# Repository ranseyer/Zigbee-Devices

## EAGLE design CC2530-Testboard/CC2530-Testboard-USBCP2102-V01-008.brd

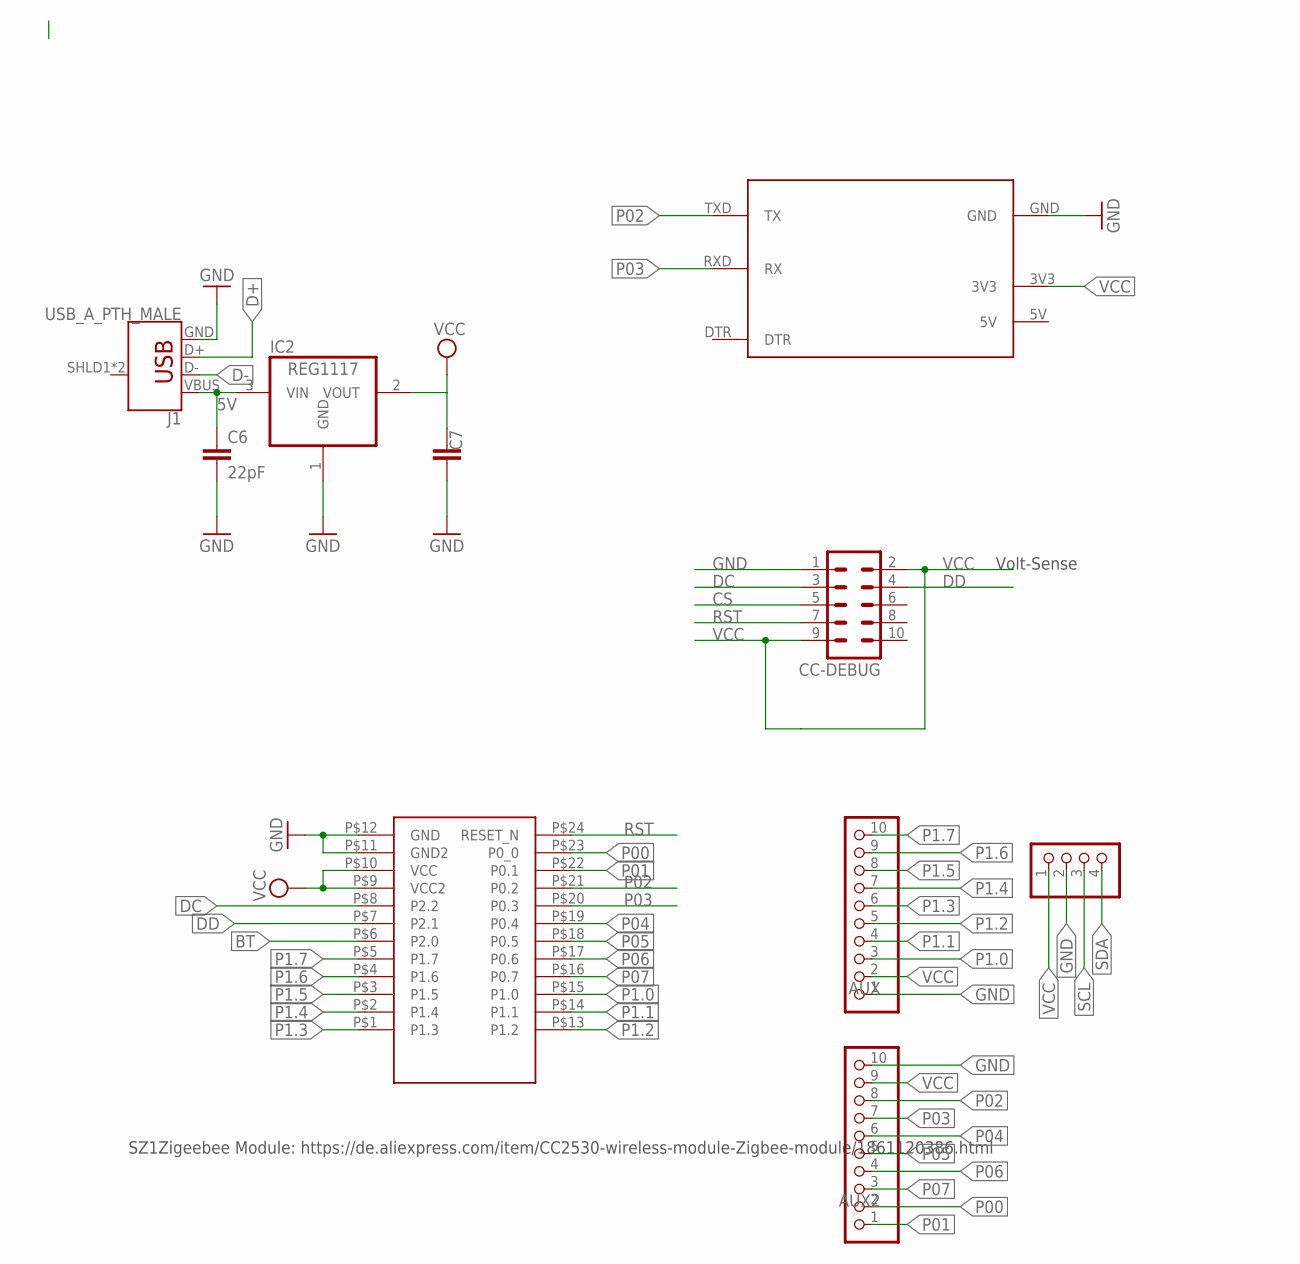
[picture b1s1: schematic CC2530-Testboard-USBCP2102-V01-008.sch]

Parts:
AUX, AUX2: PINHD-1X10_2.54-SMD-90°; 1X10SMD/90
BH1750: PINHD-1X04_2.54-S; 1X04-S
C6: 22pF; C0805
C7: C-EUC1812; C1812
CC-DEBUG: MA05-2
IC2: REG1117; SOT223
J1: USB_A_PTH_MALE; USB-A-H
U$1: CC2530; SZ1ZIGBEE-SMD
U$2: CP2101; CP2101-BEAKOUT

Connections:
5V: C6.1, IC2.3 (VIN), J1.VBUS, U$2.5V
BT: U$1.P$6 (P2.0)
CS: CC-DEBUG.5
D+: J1.D+
D-: J1.D-
DC: CC-DEBUG.3, U$1.P$8 (P2.2)
DD: CC-DEBUG.4, U$1.P$7 (P2.1)
GND: AUX.1, AUX2.10, BH1750.2, C6.2, C7.1, CC-DEBUG.1, IC2.1 (GND), J1.GND, U$1.P$11 (GND2), U$1.P$12 (GND), U$2.GND
P00: AUX2.2, U$1.P$23 (P0_0)
P01: AUX2.1, U$1.P$22 (P0.1)
P1.0: AUX.3, U$1.P$15 (P1.0)
P1.1: AUX.4, U$1.P$14 (P1.1)
P1.2: AUX.5, U$1.P$13 (P1.2)
P1.3: AUX.6, U$1.P$1 (P1.3)
P1.4: AUX.7, U$1.P$2 (P1.4)
P1.5: AUX.8, U$1.P$3 (P1.5)
P1.6: AUX.9, U$1.P$4 (P1.6)
P1.7: AUX.10, U$1.P$5 (P1.7)
P02: AUX2.8, U$1.P$21 (P0.2), U$2.TXD (TX)
P03: AUX2.7, U$1.P$20 (P0.3), U$2.RXD (RX)
P04: AUX2.6, U$1.P$19 (P0.4)
P05: AUX2.5, U$1.P$18 (P0.5)
P06: AUX2.4, U$1.P$17 (P0.6)
P07: AUX2.3, U$1.P$16 (P0.7)
RST: CC-DEBUG.7, U$1.P$24 (RESET_N)
SCL: BH1750.3
SDA: BH1750.4
VCC: AUX.2, AUX2.9, BH1750.1, C7.2, CC-DEBUG.2, CC-DEBUG.9, IC2.2 (VOUT), U$1.P$9 (VCC2), U$1.P$10 (VCC), U$2.3V3

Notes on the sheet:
Volt-Sense
SZ1Zigeebee Module: https://de.aliexpress.com/item/CC2530-wireless-module-Zigbee-module/1861120386.html

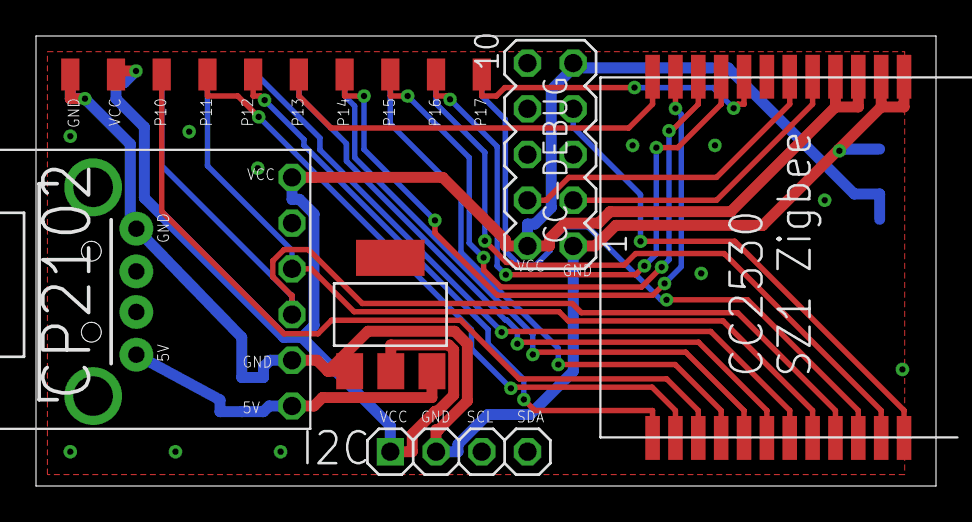
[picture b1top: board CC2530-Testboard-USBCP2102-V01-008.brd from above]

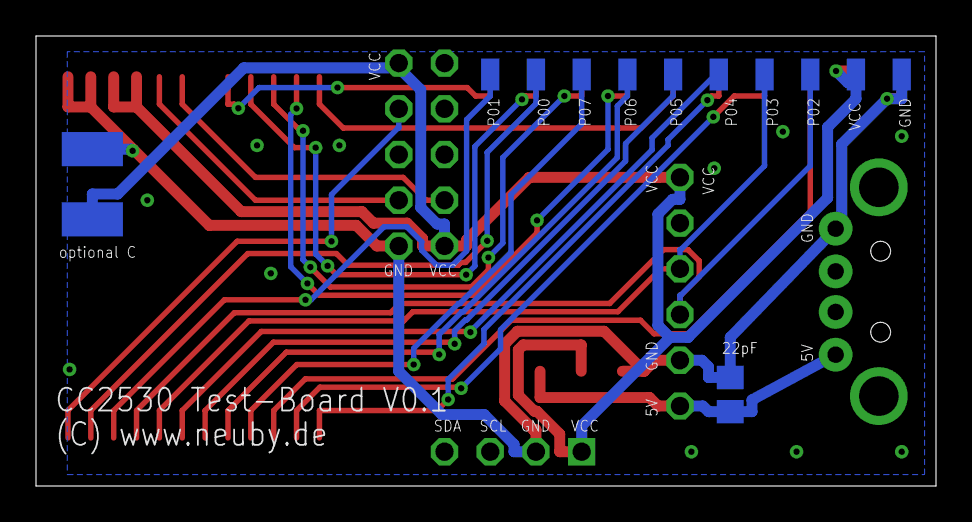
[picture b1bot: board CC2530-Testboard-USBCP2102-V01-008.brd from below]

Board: 2 copper layers, 50.0 x 25.0 mm, 10 parts (3 on the bottom side), 22 nets.

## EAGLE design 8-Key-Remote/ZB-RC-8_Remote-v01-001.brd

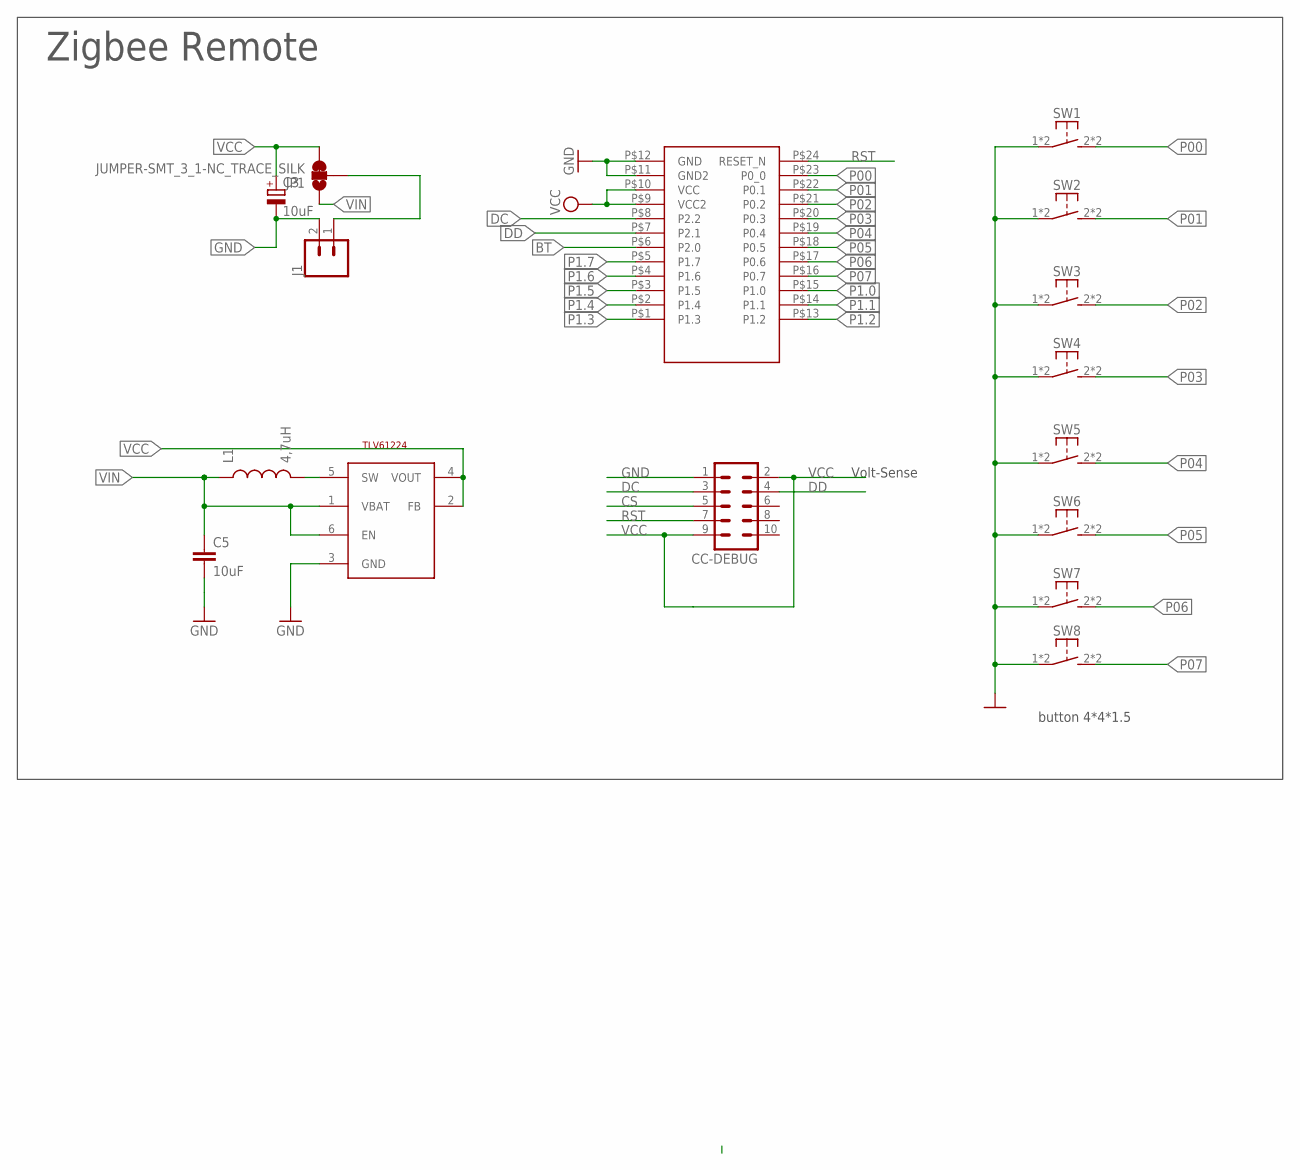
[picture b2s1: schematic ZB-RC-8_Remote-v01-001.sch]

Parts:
C3: 10uF; SMC_C
C5: 10uF; 0805
CC-DEBUG: MA05-2
J1: CONN_02PTH3; 1X02_LONGPADS
JP1: JUMPER-SMT_3_1-NC_TRACE_SILK; SMT-JUMPER_3_1-NC_TRACE_SILK
L1: 4,7uH; 0805
STEPUP: TLV61224; SOT23-6L
SW1, SW2, SW3, SW4, SW5, SW6, SW7, SW8: SW-TACTILE-TL3305; TL3305
U$1: CC2530; SZ1ZIGBEE-SMD

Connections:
BT: U$1.P$6 (P2.0)
CS: CC-DEBUG.5
DC: CC-DEBUG.3, U$1.P$8 (P2.2)
DD: CC-DEBUG.4, U$1.P$7 (P2.1)
GND: C3.-, C5.2, CC-DEBUG.1, J1.2, STEPUP.3 (GND), SW1.1, SW1.4 (P1), SW2.1, SW2.4 (P1), SW3.1, SW3.4 (P1), SW4.1, SW4.4 (P1), SW5.1, SW5.4 (P1), SW6.1, SW6.4 (P1), SW7.1, SW7.4 (P1), SW8.1, SW8.4 (P1), U$1.P$11 (GND2), U$1.P$12 (GND)
unnamed: J1.1, JP1.2
unnamed: L1.2, STEPUP.5 (SW)
P00: SW1.2 (S1), SW1.3 (S1), U$1.P$23 (P0_0)
P01: SW2.2 (S1), SW2.3 (S1), U$1.P$22 (P0.1)
P1.0: U$1.P$15 (P1.0)
P1.1: U$1.P$14 (P1.1)
P1.2: U$1.P$13 (P1.2)
P1.3: U$1.P$1 (P1.3)
P1.4: U$1.P$2 (P1.4)
P1.5: U$1.P$3 (P1.5)
P1.6: U$1.P$4 (P1.6)
P1.7: U$1.P$5 (P1.7)
P02: SW3.2 (S1), SW3.3 (S1), U$1.P$21 (P0.2)
P03: SW4.2 (S1), SW4.3 (S1), U$1.P$20 (P0.3)
P04: SW5.2 (S1), SW5.3 (S1), U$1.P$19 (P0.4)
P05: SW6.2 (S1), SW6.3 (S1), U$1.P$18 (P0.5)
P06: SW7.2 (S1), SW7.3 (S1), U$1.P$17 (P0.6)
P07: SW8.2 (S1), SW8.3 (S1), U$1.P$16 (P0.7)
RST: CC-DEBUG.7, U$1.P$24 (RESET_N)
VCC: C3.+, CC-DEBUG.2, CC-DEBUG.9, JP1.3, STEPUP.2 (FB), STEPUP.4 (VOUT), U$1.P$9 (VCC2), U$1.P$10 (VCC)
VIN: C5.1, JP1.1, L1.1, STEPUP.1 (VBAT), STEPUP.6 (EN)

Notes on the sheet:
Zigbee Remote
button 4*4*1.5
Volt-Sense

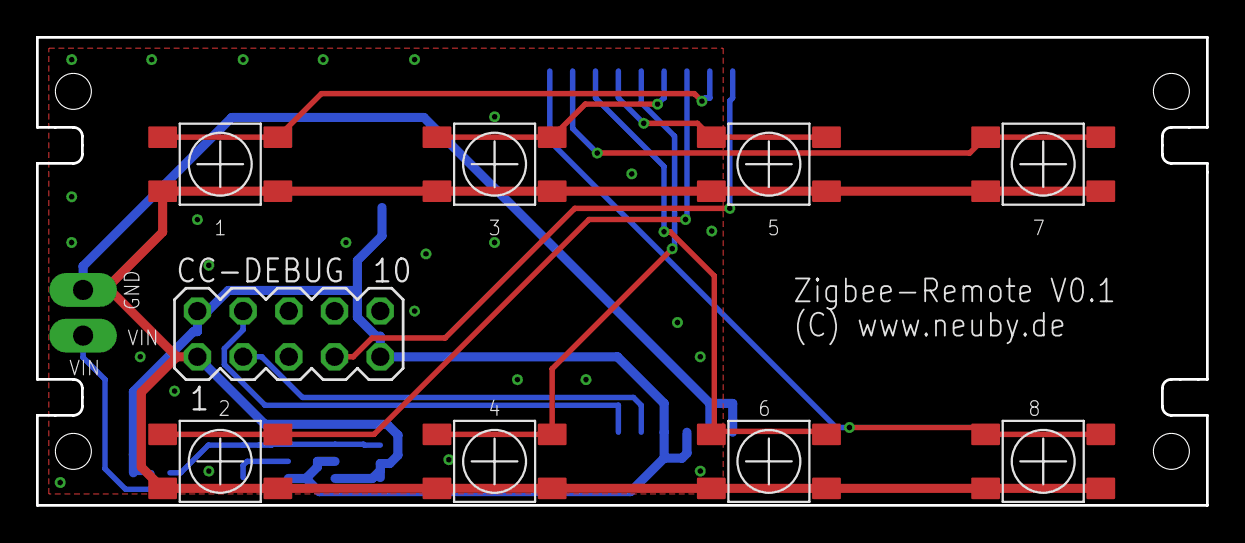
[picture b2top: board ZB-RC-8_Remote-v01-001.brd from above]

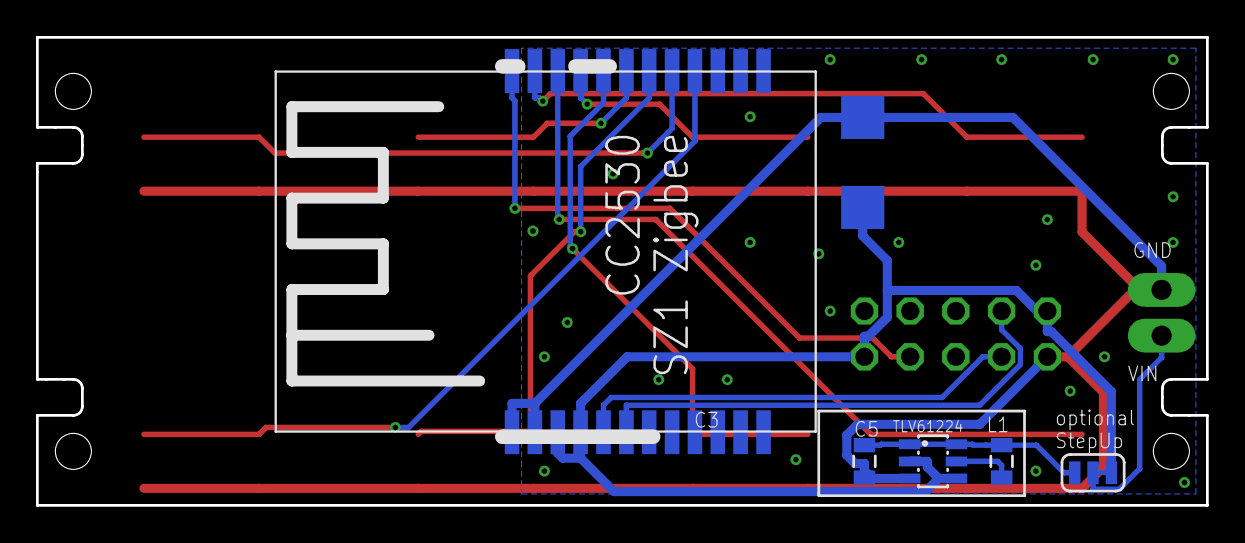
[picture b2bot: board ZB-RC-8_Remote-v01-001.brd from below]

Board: 2 copper layers, 65.0 x 26.0 mm, 16 parts (6 on the bottom side), 16 nets.

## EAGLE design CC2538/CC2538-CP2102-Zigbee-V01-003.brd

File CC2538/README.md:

# Zigbee-Devices

Yet antother CC2538 Coordinator based on the work of this cool guy: https://modkam.ru/?p=1112.

-SZ12 V2 Zigbee Module

-USB-A oder Mini-USB Socket

-Backside with out parts only close the jumpers

-minimal parts...

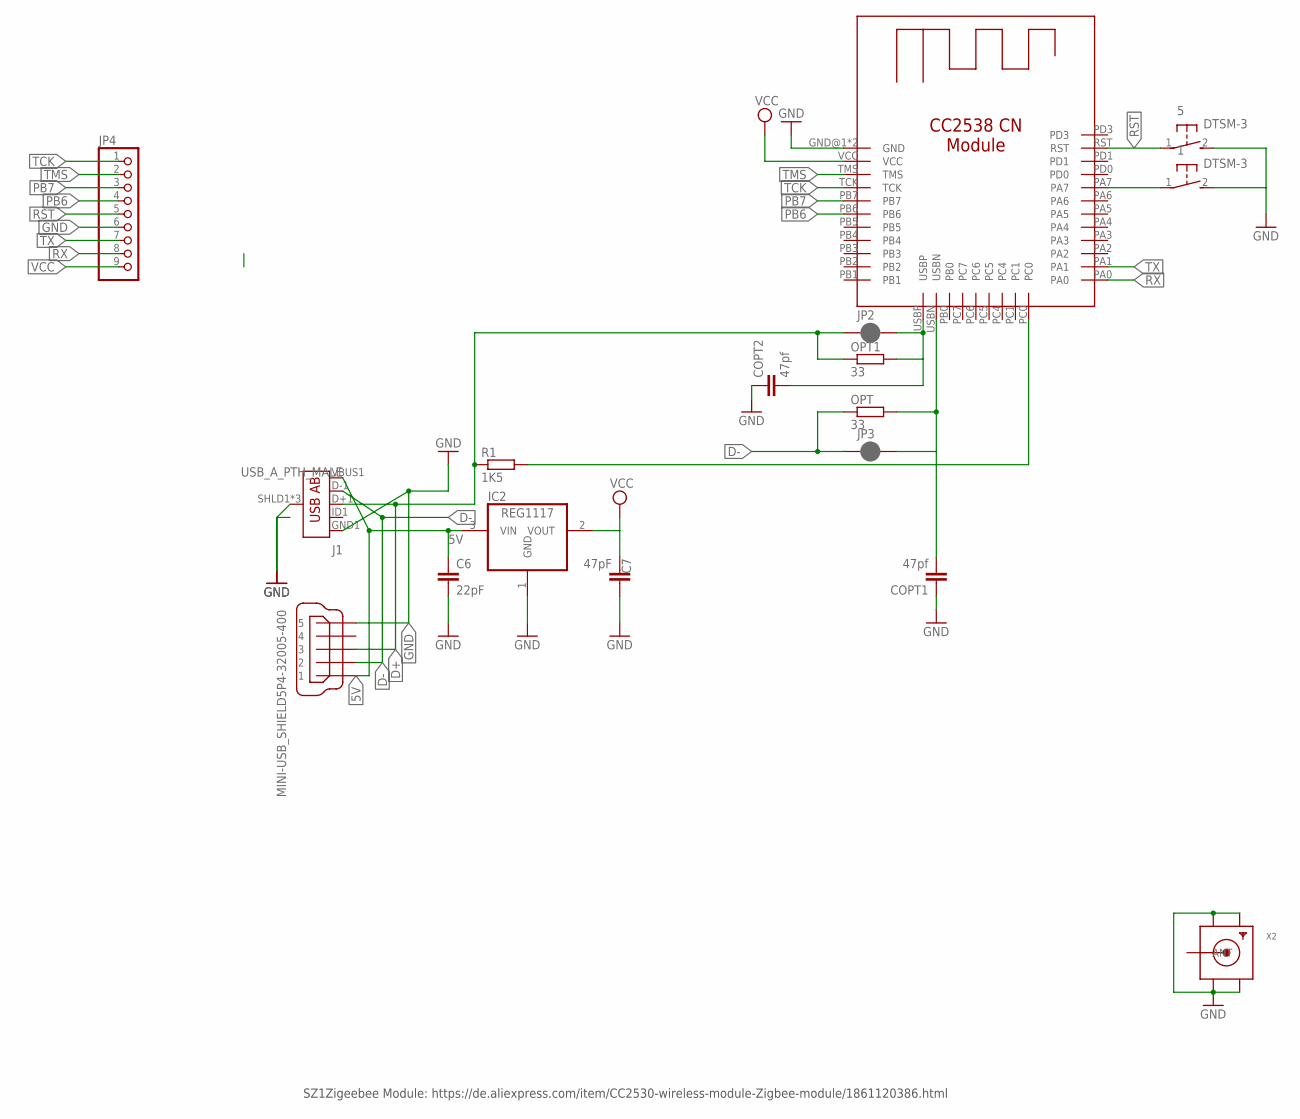
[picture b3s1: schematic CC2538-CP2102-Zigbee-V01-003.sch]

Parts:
1, 5: DTSM-3
C6: 22pF; C0805
C7: 47pF; C0805
COPT1, COPT2: 47pf; C0805
IC2: REG1117; SOT223
J1: USB_A_PTH_MALE; USB-AB-MICRO-SMD
JP2, JP3: JUMPER-SMT_2_NC_PASTE_NO-SILK; SMT-JUMPER_2_NC_PASTE_NO-SILK
JP4: PINHD-1X09_2.54-SMD-90°; 1X09SMD/90
OPT, OPT1: 33; R0805W
R1: 1K5; R0805W
U$3: CC2538-CN
X1: MINI-USB_SHIELD5P4-32005-400; 32005-400
X2: SMACONNECTOR_EDGE; SMA_EDGELAUNCH

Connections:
5V: C6.1, IC2.3 (VIN), J1.VBUS1 (VBUS), X1.1
D+: J1.D+1 (D+), JP2.1, OPT1.1, R1.1, X1.3
D-: J1.D-1 (D-), JP3.1, OPT.1, X1.2
GND: 1.2, 5.2, C6.2, C7.1, COPT1.1, COPT2.1, IC2.1 (GND), J1.GND1 (GND), J1.SHLD1 (SHIELD), J1.SHLD2 (SHIELD), J1.SHLD3 (SHIELD), JP4.6, U$3.GND@1 (GND), U$3.GND@2 (GND), X1.5, X2.GND@1 (GND4), X2.GND@2 (GND3), X2.GND@3 (GND2), X2.GND@4 (GND1)
unnamed: 1.1, U$3.PA7
unnamed: R1.2, U$3.PC0
unnamed: COPT2.2, JP2.2, OPT1.2, U$3.USBP
unnamed: COPT1.2, JP3.2, OPT.2, U$3.USBN
PB6: JP4.4, U$3.PB6
PB7: JP4.3, U$3.PB7
RST: 5.1, JP4.5, U$3.RST
RX: JP4.8, U$3.PA0
TCK: JP4.1, U$3.TCK
TMS: JP4.2, U$3.TMS
TX: JP4.7, U$3.PA1
VCC: C7.2, IC2.2 (VOUT), JP4.9, U$3.VCC

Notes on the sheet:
SZ1Zigeebee Module: https://de.aliexpress.com/item/CC2530-wireless-module-Zigbee-module/1861120386.html

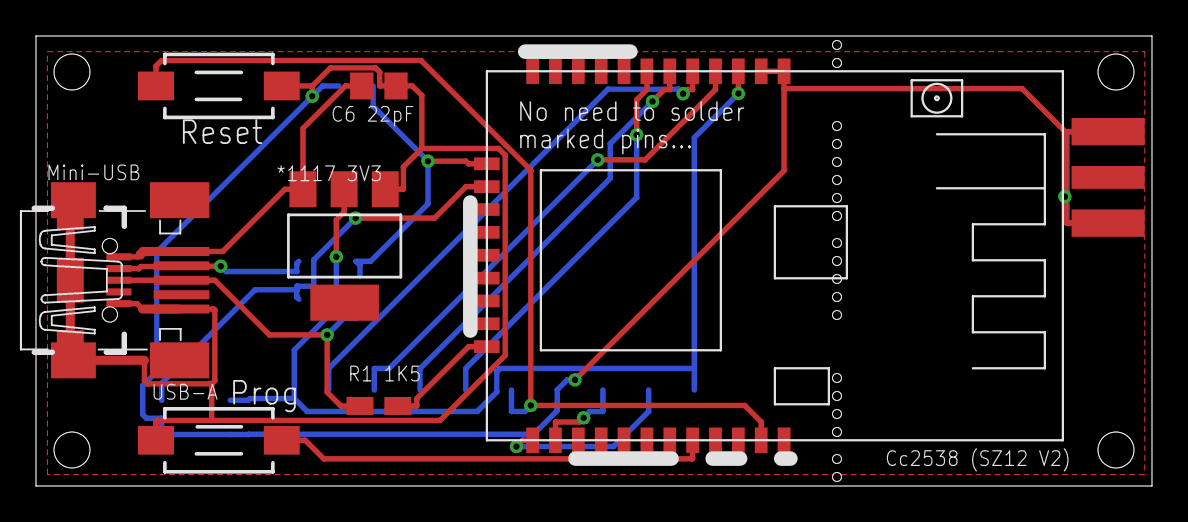
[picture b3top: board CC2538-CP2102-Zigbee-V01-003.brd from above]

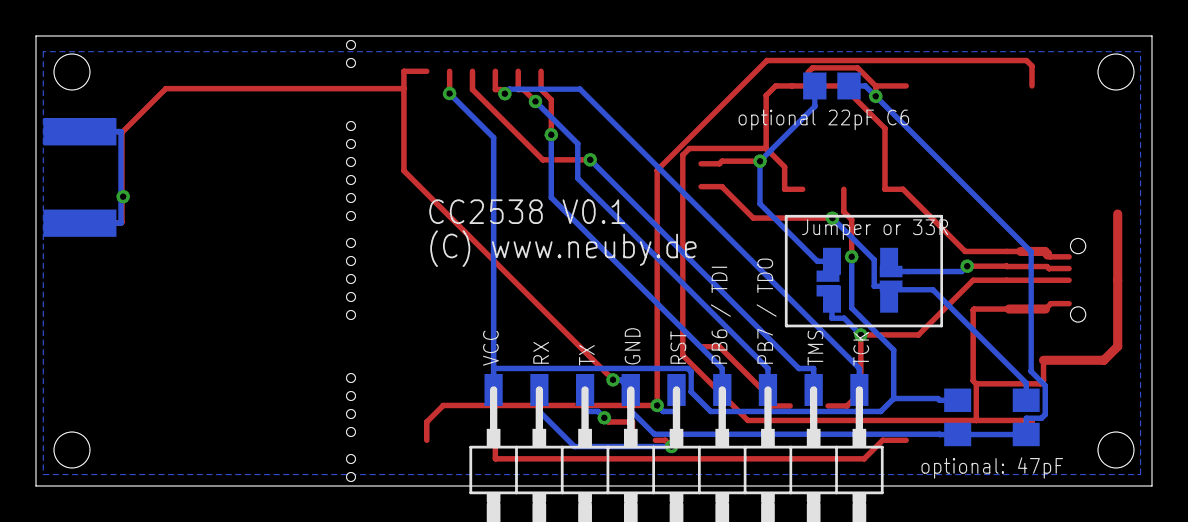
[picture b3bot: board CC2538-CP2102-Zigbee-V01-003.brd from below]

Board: 2 copper layers, 62.0 x 25.0 mm, 17 parts (8 on the bottom side), 16 nets.

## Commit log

2021-01-19 CC2530 moved from homeautomatics repo
2021-01-19 New: CC2538 Coordinator
2021-01-19 Readme
2021-01-19 images
2021-01-29 Zigbee, ...
2021-03-06 Pics

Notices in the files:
parts and their libraries:
SparkFun-Passives: Licensing: CC v3.0 Share-Alike You are welcome to use this library for commercial purposes.
SparkFun-Connectors: Licensing: Creative Commons ShareAlike 4.0 International - https://creativecommons.org/licenses/by-sa/4.0
